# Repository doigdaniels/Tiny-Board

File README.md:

# Tiny-Board
A small, battery-powered carrier board for the Raspberry Pi CM4 (and other compatible CM4 replacments).
More updates coming soon!
## Pictures

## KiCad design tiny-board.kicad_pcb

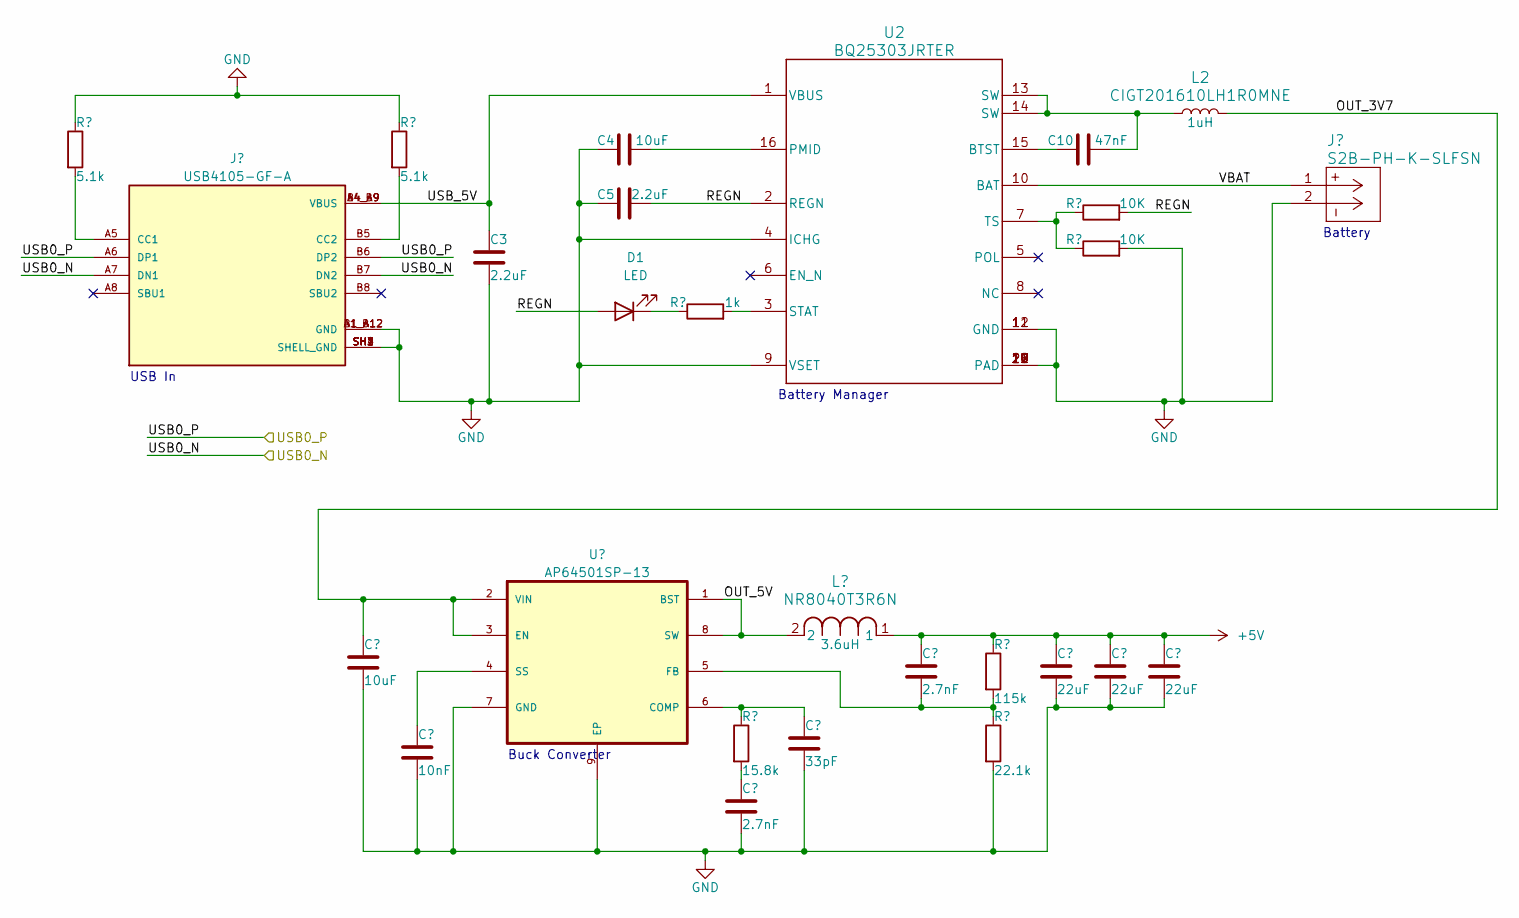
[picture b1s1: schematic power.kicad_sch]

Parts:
C1, C4: 10uF; CAPC2012X140N
C2: 10nF; CAPC2012X140N
C3, C5: 2.2uF; CAPC2012X140N
C6, C8: 2.7nF; CAPC2012X140N
C7: 33pF; CAPC2012X140N
C9, C11, C12: 22uF; CAPC2012X140N
C10: 47nF; CAPC2012X140N
D1: LED; RC0603FR-071K5L_RESC1607X60N
J1: USB4105-GF-A; USB4105-GF-A_GCT_USB4105-GF-A; PARTREV B3
J2: S2B-PH-K-SLFSN; CONN_S2B-PH-K-S_JST
L1: NR8040T3R6N; IND_TAIYO_NR8040_TAY
L2: CIGT201610LH1R0MNE; RES_CIGT201610_SAM
R1, R2: 5.1k; RC0603FR-071K5L_RESC1607X60N
R3: 1k; RC0603FR-071K5L_RESC1607X60N
R4: 15.8k; RC0603FR-071K5L_RESC1607X60N
R5: 115k; RC0603FR-071K5L_RESC1607X60N
R6: 22.1k; RC0603FR-071K5L_RESC1607X60N
R7, R8: 10K; RC0603FR-071K5L_RESC1607X60N
U1: AP64501SP-13; AP64501SP-13_SOIC127P600X170-9N
U2: BQ25303JRTER; RTE0016C

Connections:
+5V: C8.1, C9.1, C11.1, C12.1, L1.1, R5.1; also elsewhere on the board
/POWER/OUT_3V7: C1.1, L2.2, U1.2 (VIN), U1.3 (EN)
/POWER/OUT_5V: L1.2, U1.1 (BST), U1.8 (SW)
/POWER/REGN: C5.2, D1.2 (A), R7.2, U2.2 (REGN)
/POWER/USB0_N: J1.A7 (DN1), J1.B7 (DN2); also elsewhere on the board
/POWER/USB0_P: J1.A6 (DP1), J1.B6 (DP2); also elsewhere on the board
/POWER/USB_5V: C3.1, J1.A4_B9 (VBUS), J1.B4_A9 (VBUS), U2.1 (VBUS)
/POWER/VBAT: J2.1, U2.10 (BAT)
GND: C1.2, C2.2, C3.2, C4.1, C5.1, C6.2, C7.2, C9.2, C11.2, C12.2, J1.A1_B12 (GND), J1.B1_A12 (GND), J1.SH1 (SHELL_GND), J1.SH2 (SHELL_GND), J1.SH3 (SHELL_GND), J1.SH4 (SHELL_GND), J2.2, R1.1, R2.1, R6.2, R8.2, U1.7 (GND), U1.9 (EP), U2.4 (ICHG), U2.9 (VSET), U2.11 (GND), U2.12 (GND), U2.17 (PAD), U2.18 (PAD), U2.19 (PAD), U2.20 (PAD), U2.21 (PAD), U2.22 (PAD); also elsewhere on the board
unnamed: C6.1, R4.2
unnamed: C10.2, L2.1, U2.13 (SW), U2.14 (SW)
unnamed: D1.1 (K), R3.1
unnamed: J1.A5 (CC1), R1.2
unnamed: J1.B5 (CC2), R2.2
unnamed: C7.1, R4.1, U1.6 (COMP)
unnamed: C8.2, R5.2, R6.1, U1.5 (FB)
unnamed: C2.1, U1.4 (SS)
unnamed: C10.1, U2.15 (BTST)
unnamed: C4.2, U2.16 (PMID)
unnamed: R3.2, U2.3 (STAT)
unnamed: R7.1, R8.1, U2.7 (TS)

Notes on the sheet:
Battery
Buck Converter
USB In
Battery Manager

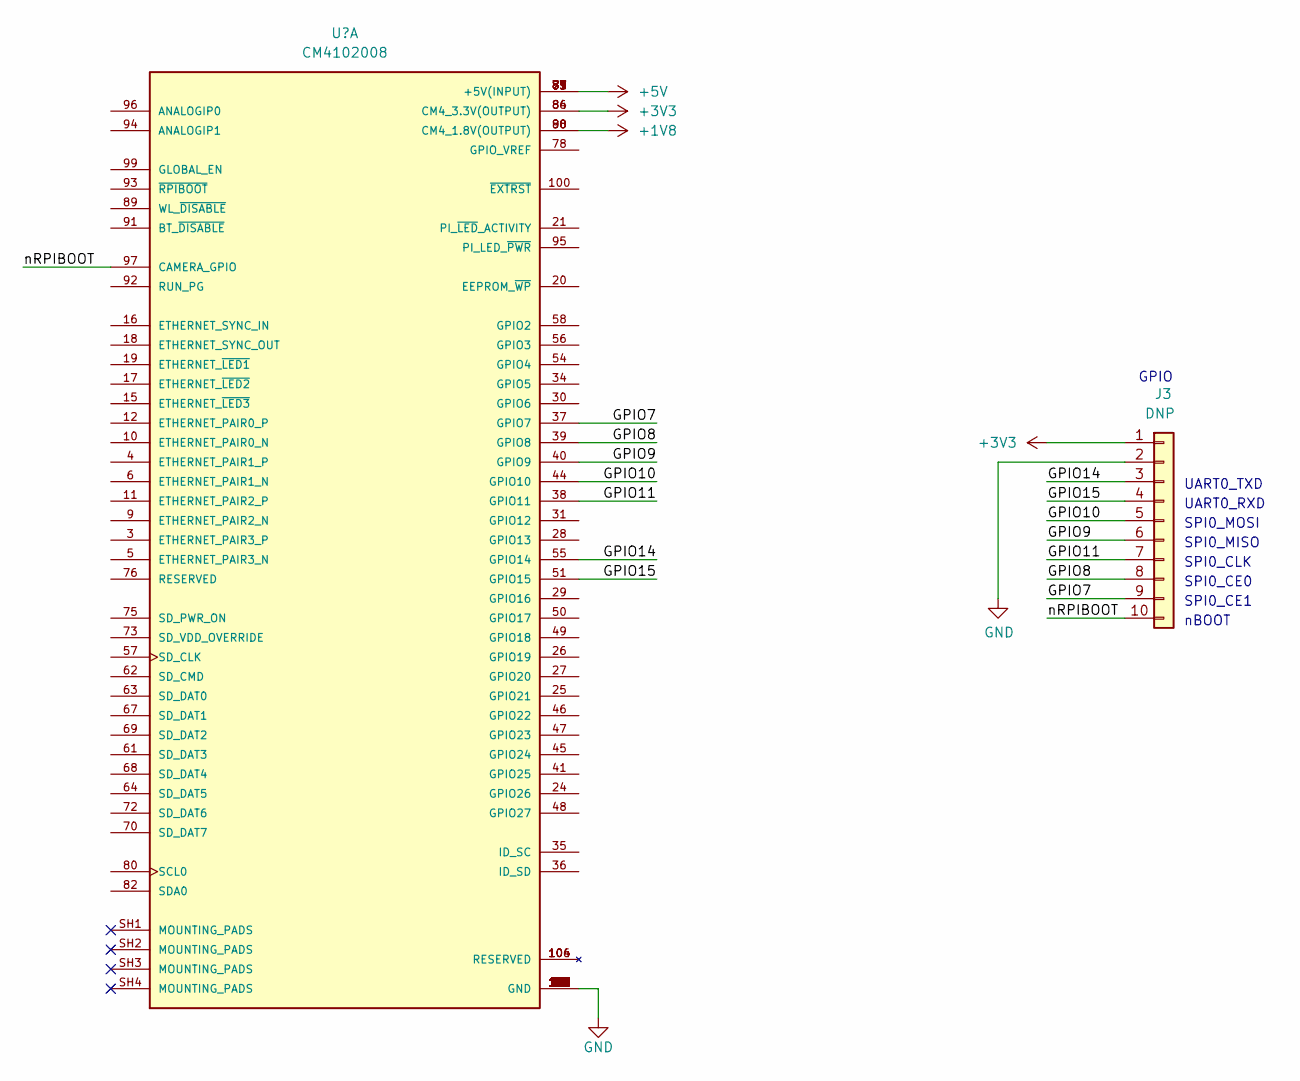
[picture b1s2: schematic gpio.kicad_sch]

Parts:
J3: DNP; PinHeader_1x10_P2.54mm_Vertical
U3: CM4102008; CM4102008_MODULE_CM4102008; PARTREV 2021-10-12

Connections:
+1V8: U3.88 (CM4_1.8V(OUTPUT)), U3.90 (CM4_1.8V(OUTPUT))
+3V3: J3.1, U3.84 (CM4_3.3V(OUTPUT)), U3.86 (CM4_3.3V(OUTPUT))
+5V: U3.77 (+5V(INPUT)), U3.79 (+5V(INPUT)), U3.81 (+5V(INPUT)), U3.83 (+5V(INPUT)), U3.85 (+5V(INPUT)), U3.87 (+5V(INPUT)); also elsewhere on the board
/GPIO/GPIO7: J3.9, U3.37 (GPIO7)
/GPIO/GPIO8: J3.8, U3.39 (GPIO8)
/GPIO/GPIO9: J3.6, U3.40 (GPIO9)
/GPIO/GPIO10: J3.5, U3.44 (GPIO10)
/GPIO/GPIO11: J3.7, U3.38 (GPIO11)
/GPIO/GPIO14: J3.3, U3.55 (GPIO14)
/GPIO/GPIO15: J3.4, U3.51 (GPIO15)
/GPIO/nRPIBOOT: J3.10, U3.97 (CAMERA_GPIO)
GND: J3.2, U3.1 (GND), U3.2 (GND), U3.7 (GND), U3.8 (GND), U3.13 (GND), U3.14 (GND), U3.22 (GND), U3.23 (GND), U3.32 (GND), U3.33 (GND), U3.42 (GND), U3.43 (GND), U3.52 (GND), U3.53 (GND), U3.59 (GND), U3.60 (GND), U3.65 (GND), U3.66 (GND), U3.71 (GND), U3.74 (GND), U3.98 (GND), U3.107 (GND), U3.108 (GND), U3.113 (GND), U3.114 (GND), U3.119 (GND), U3.120 (GND), U3.125 (GND), U3.126 (GND), U3.131 (GND), U3.132 (GND), U3.137 (GND), U3.138 (GND), U3.144 (GND), U3.150 (GND), U3.155 (GND), U3.156 (GND), U3.161 (GND), U3.162 (GND), U3.167 (GND), U3.168 (GND), U3.173 (GND), U3.174 (GND), U3.179 (GND), U3.180 (GND), U3.185 (GND), U3.186 (GND), U3.191 (GND), U3.192 (GND), U3.197 (GND), U3.198 (GND); also elsewhere on the board

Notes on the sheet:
SPI0_MISO
UART0_RXD
SPI0_CE1
SPI0_CE0
nBOOT
UART0_TXD
SPI0_CLK
SPI0_MOSI
GPIO

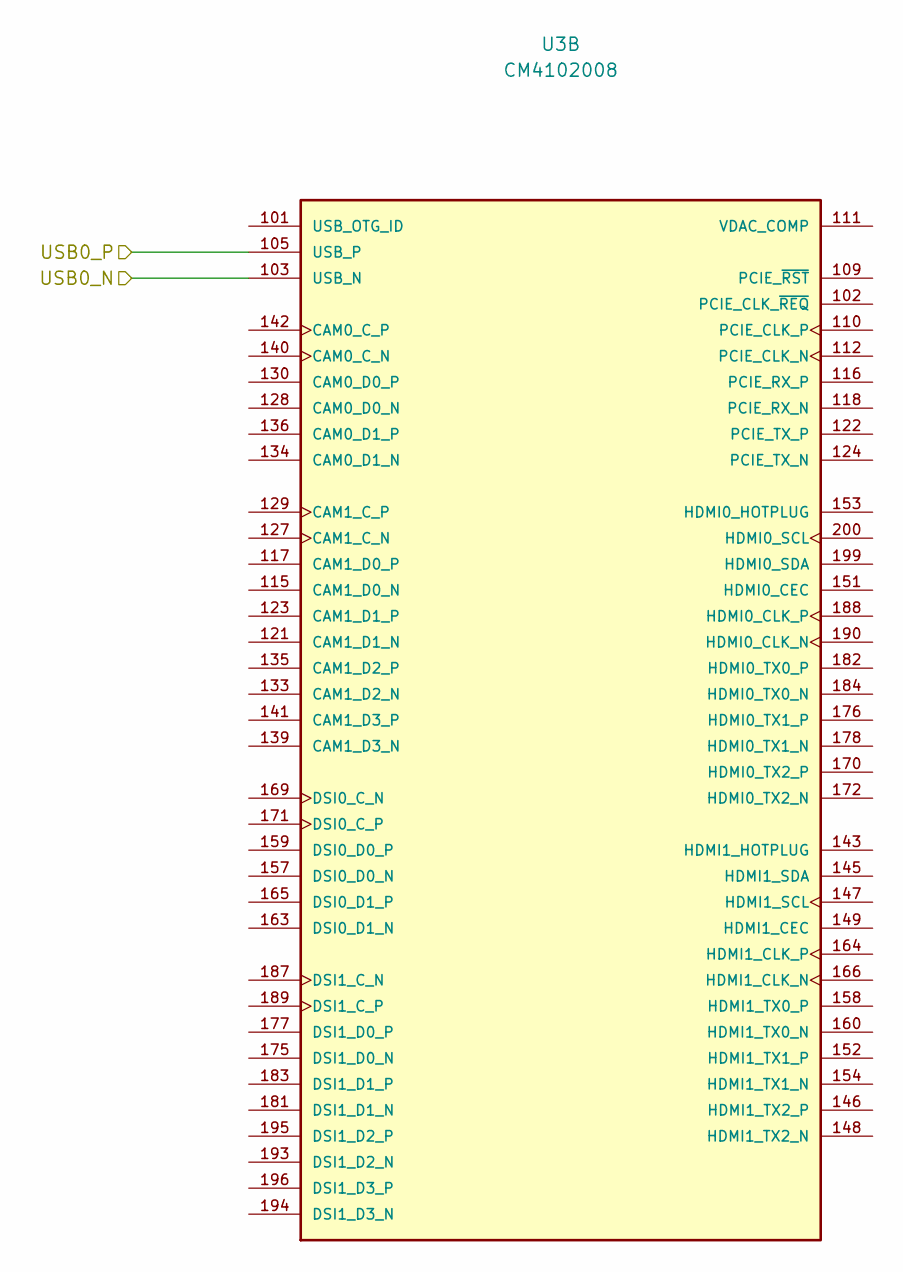
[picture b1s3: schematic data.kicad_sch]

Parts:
U3: CM4102008; CM4102008_MODULE_CM4102008; PARTREV 2021-10-12

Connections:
/POWER/USB0_N: U3.103 (USB_N); also elsewhere on the board
/POWER/USB0_P: U3.105 (USB_P); also elsewhere on the board

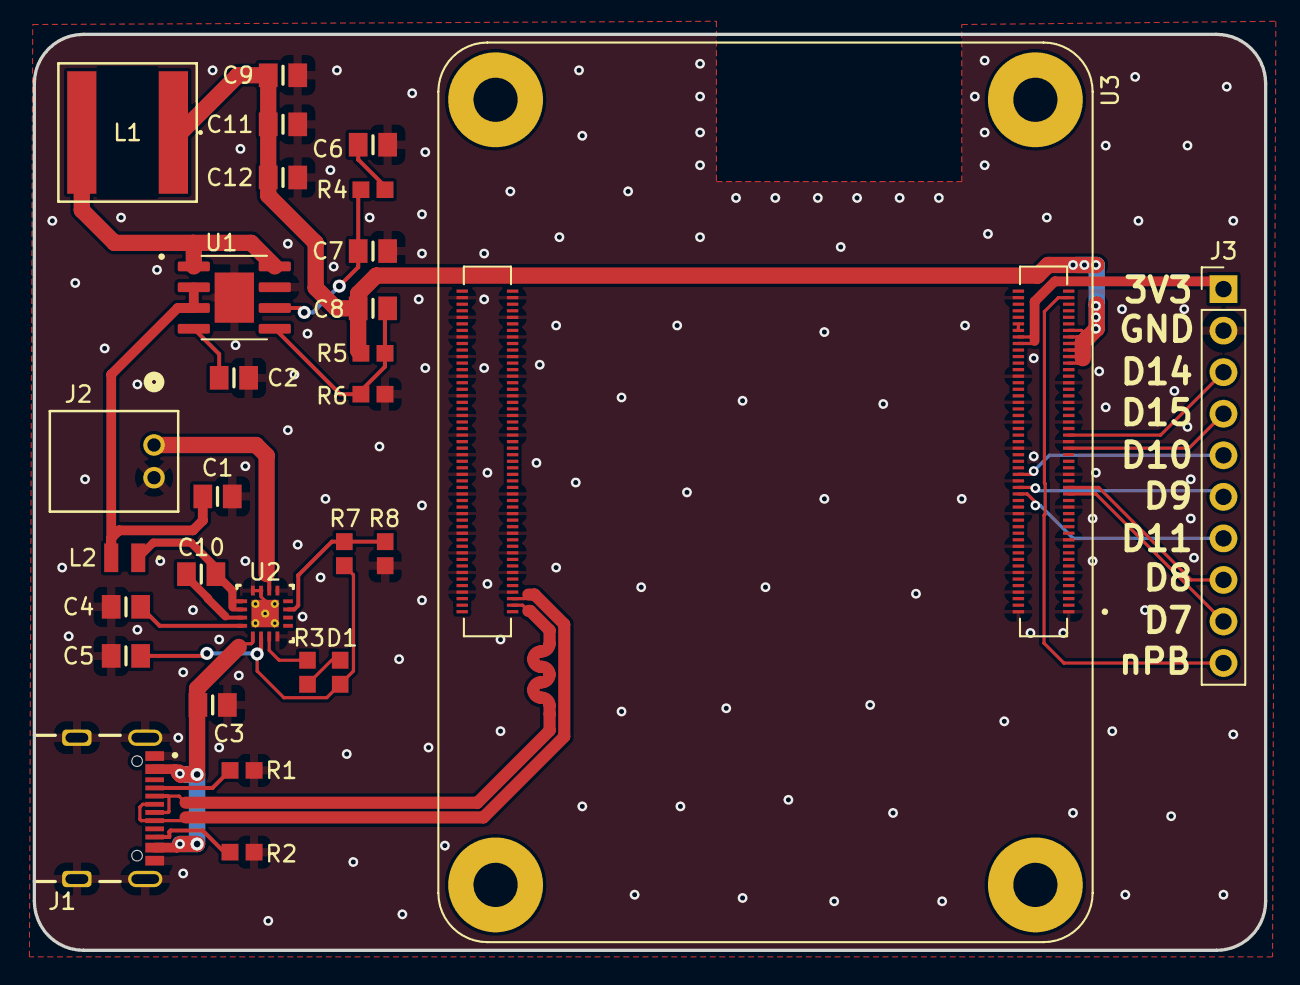
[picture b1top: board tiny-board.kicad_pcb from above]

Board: 2 copper layers, 75.3 x 56.0 mm, 29 parts (0 on the bottom side), 31 nets.
